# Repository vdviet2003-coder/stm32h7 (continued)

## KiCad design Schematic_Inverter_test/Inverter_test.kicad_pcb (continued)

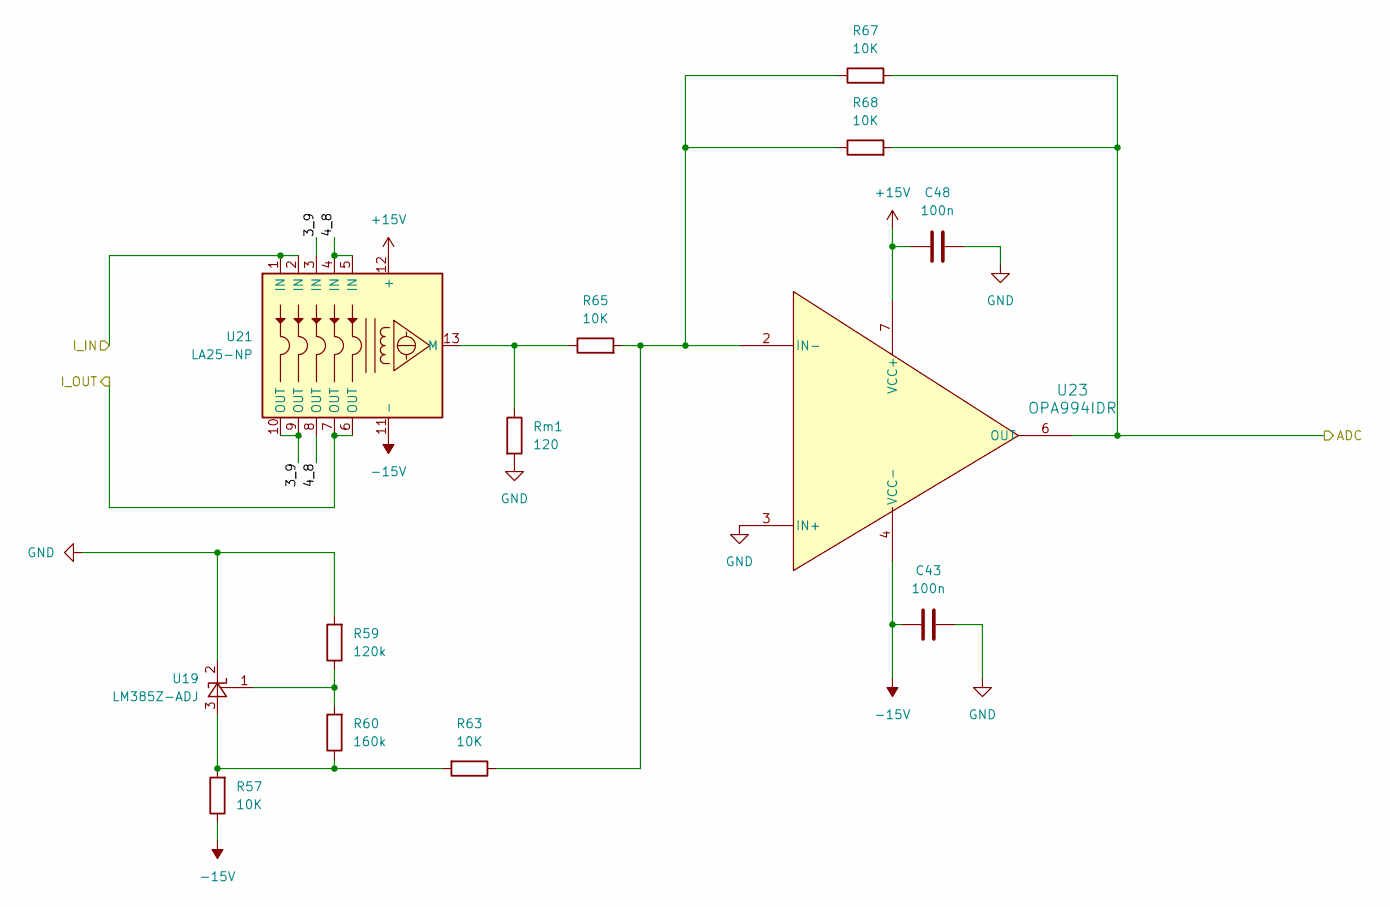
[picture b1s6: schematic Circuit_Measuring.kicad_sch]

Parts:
C43, C48: 100n; C_1206_3216Metric_Pad1.33x1.80mm_HandSolder
R57, R63, R65, R67, R68: 10K; C_1206_3216Metric_Pad1.33x1.80mm_HandSolder
R59: 120k; R_0805_2012Metric_Pad1.20x1.40mm_HandSolder
R60: 160k; C_1206_3216Metric_Pad1.33x1.80mm_HandSolder
Rm1: 120; C_1206_3216Metric_Pad1.33x1.80mm_HandSolder
U19: LM385Z-ADJ; TO-92_Inline
U21: LA25-NP; LEM_LA25-NP
U23: OPA994IDR; SOIC8_D_TEX

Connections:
+15V: C48.1, U21.12 (+), U23.7 (VCC+); also elsewhere on the board
-15V: C43.2, R57.1, U21.11 (-), U23.4 (VCC-); also elsewhere on the board
/Three Phase/Circuit_Measuring/3_9: U21.3 (IN), U21.9 (OUT), U21.10 (OUT)
/Three Phase/Circuit_Measuring/4_8: U21.4 (IN), U21.5 (IN), U21.8 (OUT)
/Three Phase/U: U21.1 (IN), U21.2 (IN); also elsewhere on the board
/Three Phase/U_ADC: R67.2, R68.2, U23.6 (OUT); also elsewhere on the board
/Three Phase/U_OUT: U21.6 (OUT), U21.7 (OUT); also elsewhere on the board
GND: C43.1, C48.2, R59.2, Rm1.2, U19.2 (K), U23.3 (IN+); also elsewhere on the board
unnamed: R57.2, R60.1, R63.2, U19.3 (A)
unnamed: R59.1, R60.2, U19.1 (FB)
unnamed: R65.1, Rm1.1, U21.13 (M)
unnamed: R63.1, R65.2, R67.1, R68.1, U23.2 (IN-)

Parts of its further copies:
C67, C68: 100n; C_1206_3216Metric_Pad1.33x1.80mm_HandSolder
R58, R64, R66, R69, R70: 10K; C_1206_3216Metric_Pad1.33x1.80mm_HandSolder
R61: 120k; R_0805_2012Metric_Pad1.20x1.40mm_HandSolder
R62: 160k; C_1206_3216Metric_Pad1.33x1.80mm_HandSolder
Rm2: 120; C_1206_3216Metric_Pad1.33x1.80mm_HandSolder
U20: LM385Z-ADJ; TO-92_Inline
U22: LA25-NP; LEM_LA25-NP
U24: OPA994IDR; SOIC8_D_TEX

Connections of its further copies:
+15V: C68.1, U22.12 (+), U24.7 (VCC+); also elsewhere on the board
-15V: C67.2, R58.1, U22.11 (-), U24.4 (VCC-); also elsewhere on the board
/Three Phase/Circuit_Measuring1/3_9: U22.3 (IN), U22.9 (OUT), U22.10 (OUT)
/Three Phase/Circuit_Measuring1/4_8: U22.4 (IN), U22.5 (IN), U22.8 (OUT)
/Three Phase/V: U22.1 (IN), U22.2 (IN); also elsewhere on the board
/Three Phase/V_ADC: R69.2, R70.2, U24.6 (OUT); also elsewhere on the board
/Three Phase/V_OUT: U22.6 (OUT), U22.7 (OUT); also elsewhere on the board
GND: C67.1, C68.2, R61.2, Rm2.2, U20.2 (K), U24.3 (IN+); also elsewhere on the board
unnamed: R58.2, R62.1, R64.2, U20.3 (A)
unnamed: R61.1, R62.2, U20.1 (FB)
unnamed: R66.1, Rm2.1, U22.13 (M)
unnamed: R64.1, R66.2, R69.1, R70.1, U24.2 (IN-)

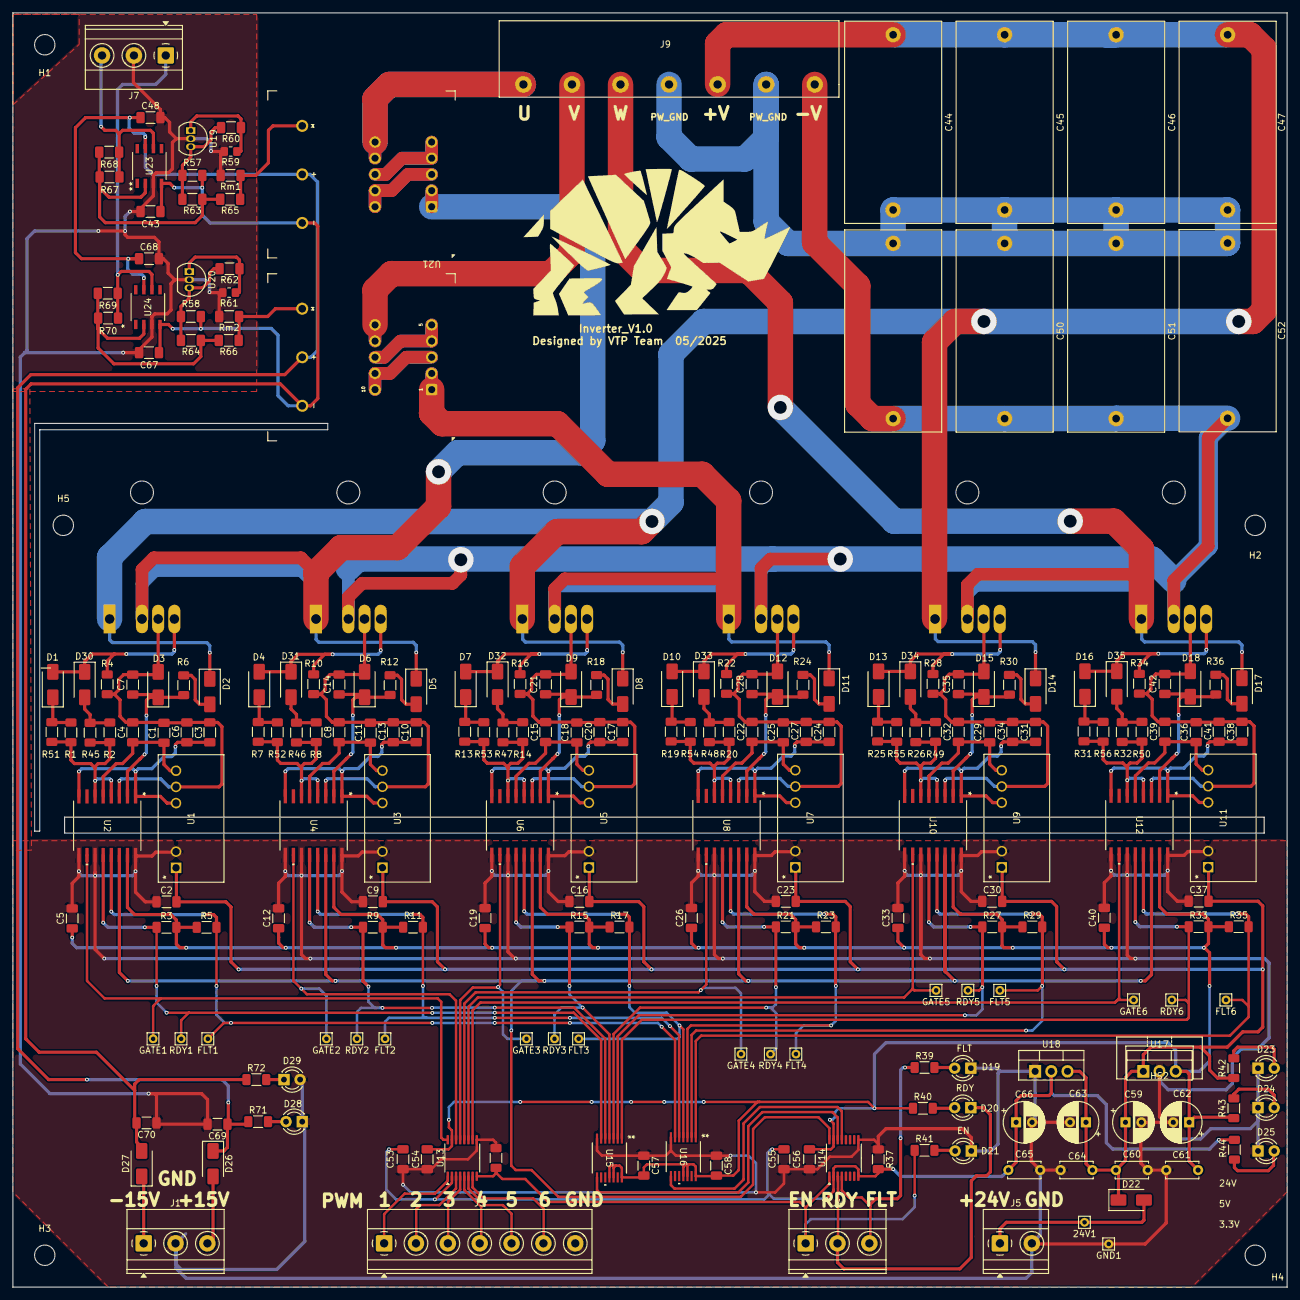
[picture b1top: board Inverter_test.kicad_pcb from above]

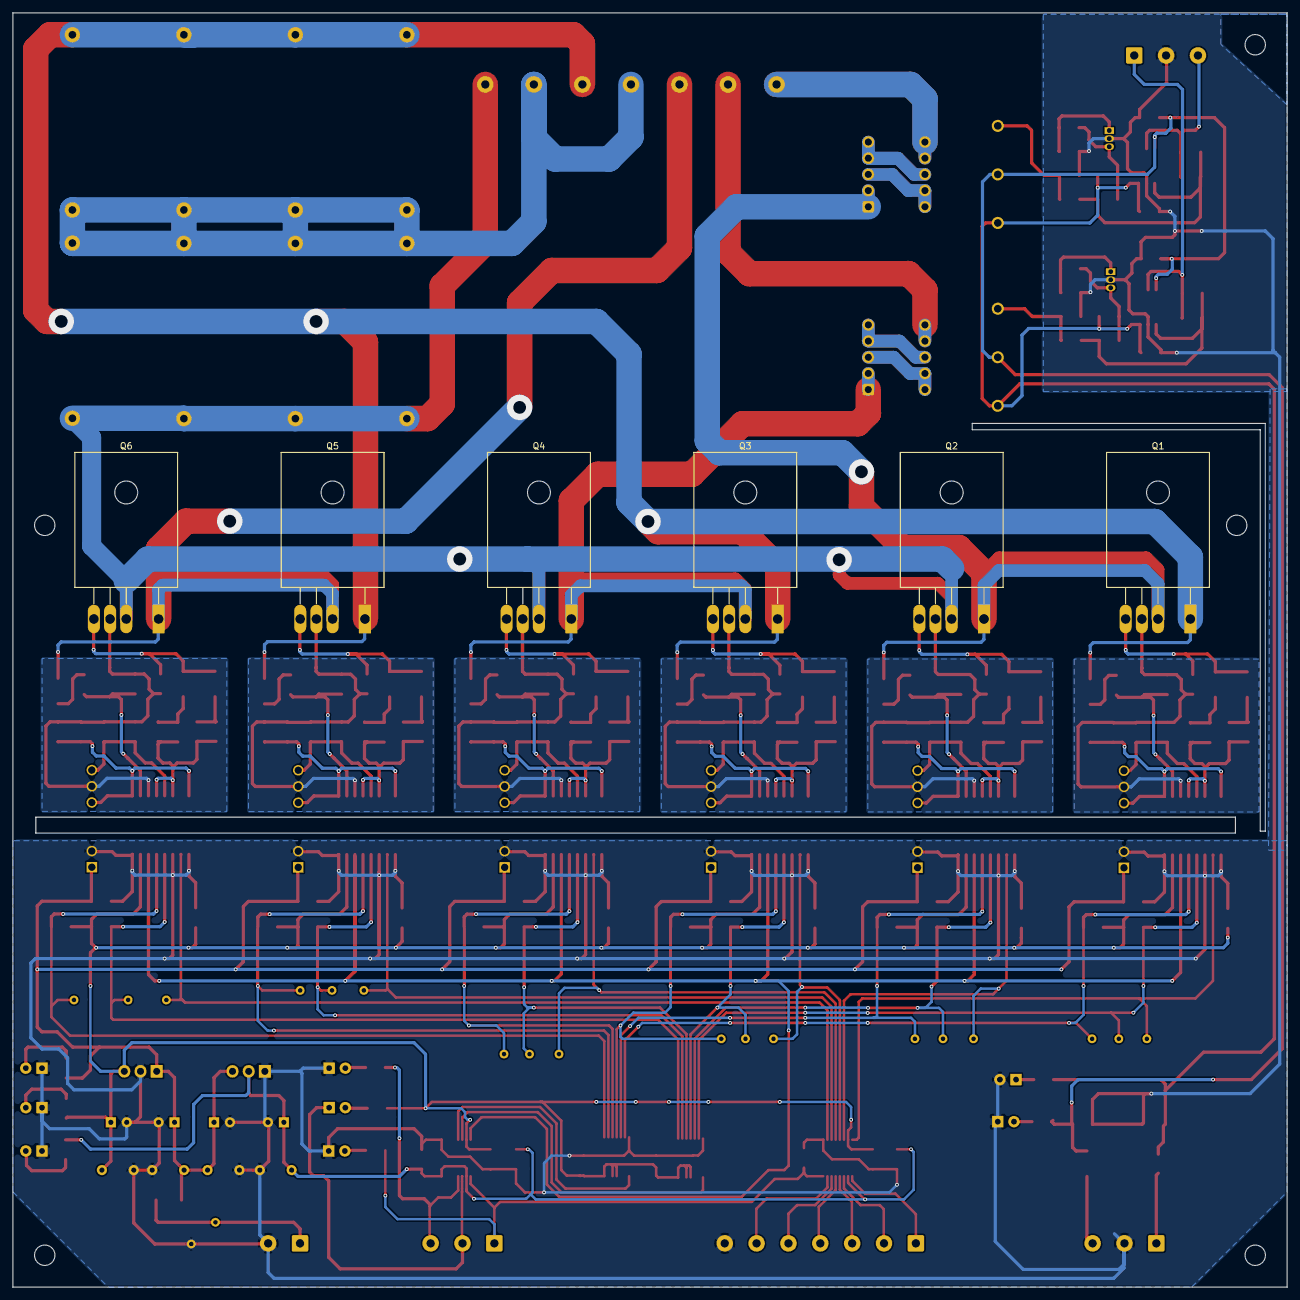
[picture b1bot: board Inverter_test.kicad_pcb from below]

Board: 2 copper layers, 200.0 x 200.0 mm, 241 parts (6 on the bottom side), 123 nets.

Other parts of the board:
HS2: Heatsink; Heatsink_Stonecold_HS-S01_13.21x6.35mm

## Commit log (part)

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2026-03-17 update tai lieu
2026-03-21 add function Pid
2026-03-25 change sensor
2026-04-07 run with encoder
2026-04-07 update sensor
2026-04-07 no encoder
2026-06-04 sensorless
